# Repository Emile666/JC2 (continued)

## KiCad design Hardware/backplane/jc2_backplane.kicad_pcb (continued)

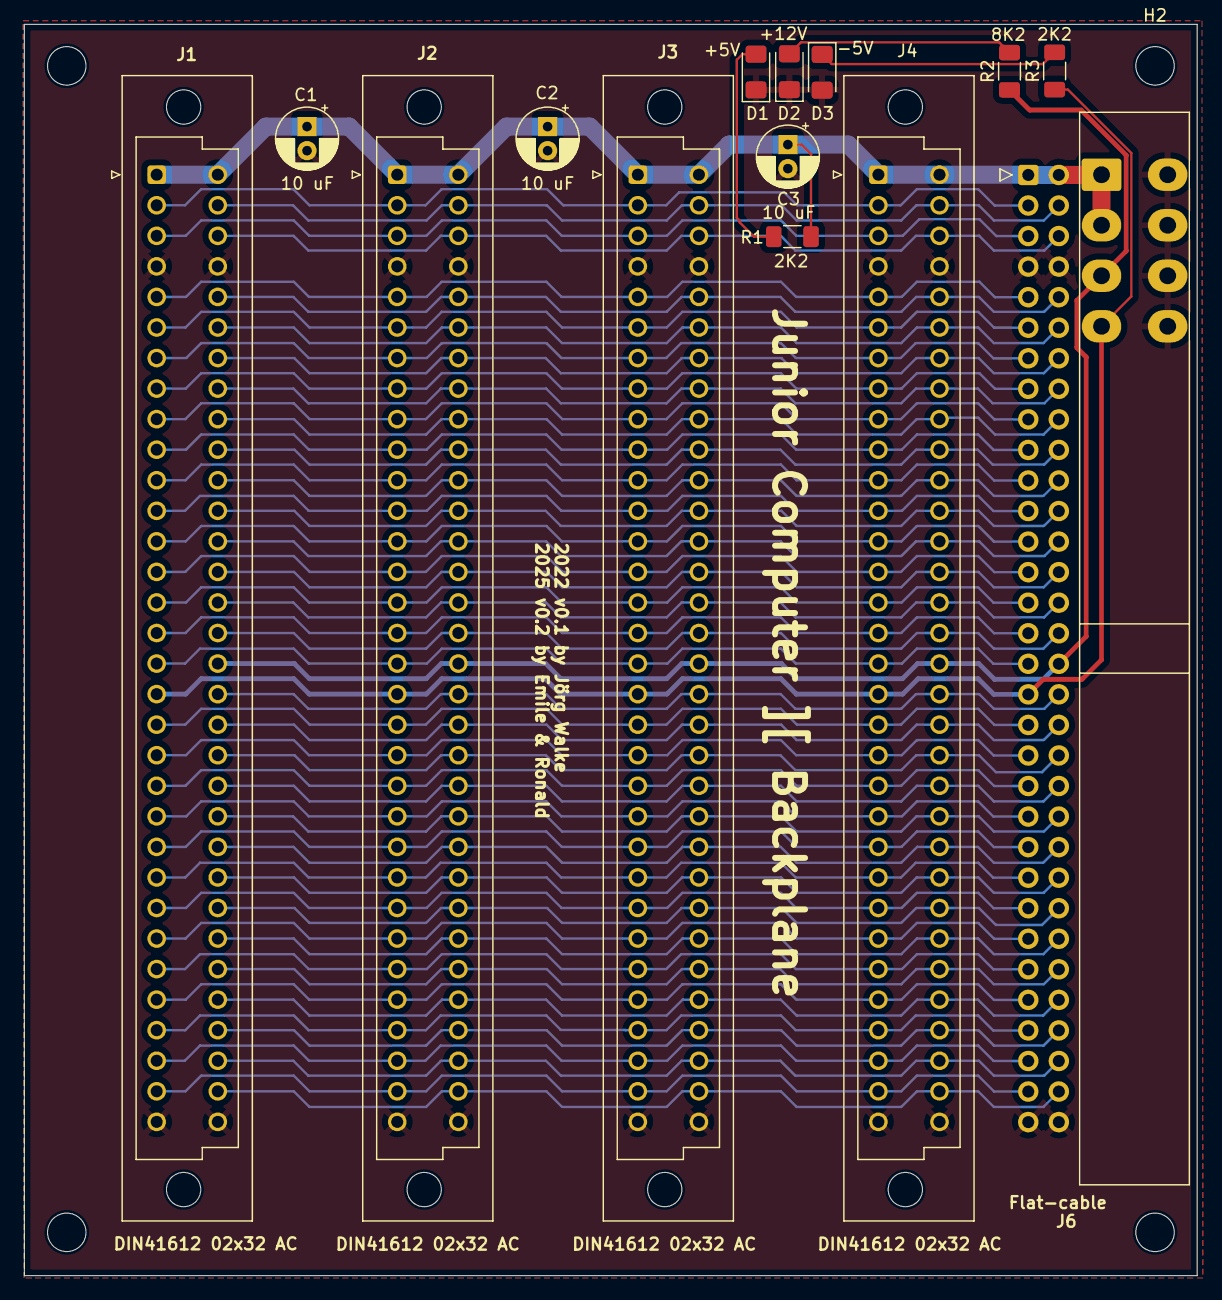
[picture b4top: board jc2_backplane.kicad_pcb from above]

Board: 2 copper layers, 97.5 x 104.0 mm, 19 parts (1 on the bottom side), 63 nets.

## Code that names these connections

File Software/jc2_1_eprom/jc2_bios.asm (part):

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		LDA     #$21
		TAY
		STA     PBDD		; turn speaker on
BEEPLOOP	STY     PBD		; set PB0 high
		LDA     #$01
		JSR     DELAY		; delay of ~1ms
		DEY
		STY	PBD		; set PB0 low
		LDA	#$01
		JSR	DELAY		; delay of ~1ms
		LDY	#$21
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; Jump to original Junior Computer reset vector ********************************

;*******************************************************************************
JCRESET		LDA	#$06			; set PB5 = L (WRITE)
		STA	PBD
		SEI
		JSR     INITVECT
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                BNE     INIT_VIA        ; is standard input device still TTY?
                JSR	DETECT_ASCIIKBD	; yes, check if ASCII keyboard available, else skip it
INIT_VIA	LDY	#PORTB
		LDA	#%01001110	; SDA=0,/CAS_MOT=1,CAS_SENSE=0,CAS_WR=0,/SPI_LOAD=1,SPI_CS=1,/SND_WE=1,SCL=0
		STA	VIA_STATUS	; store current PortB output status
		STA	(IOBASE),Y	; set SDA as input to pull it high, set SCL as input to pull it high
		LDY	#DDRB		; initialize data direction of port B
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		BEQ	READMODE	; yes, check if data available
		JSR	SETPPORTIN	; no, first set parallel port as an input
READMODE	CLC			; set to no char present
		BIT	WRDC		; test PA7 (DATA_AVAIL)
		BVC	NODATA		; no new data, just exit with C = 0
		LDA	WRDC		; clear PA7 flag
		LDA	PAD		; load keyboard ASCII code from port A
		AND	#%01111111	; clear MSB
DATA_AVAIL	SEC			; and set C = 1, char present
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		LDA	#$BE		; initialize handshake line I/O on port b
		CMP	PBDD		; already initialized?
		BEQ	SETHSK		; yes, just set output values
		STA	PBDD		; no, PB7 = /strobe, PB6 = busy, PB5 = r/w, PB0 = speaker off
SETHSK		LDA	#$86		; set handshake lines to their initial values
		STA	PBD		; r/w = L, strobe = H, PB1,PB2 = H -> hex-kbd disabled; speaker = H
		LDA	#$FF		; all port A lines are outputs
		STA	PADD
		PLA			; reload character in A
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
PPORTIN		JSR	SETPPORTIN	; set parallel port as input
		CLC
		BIT	PBD		; check if /STROBE = 0
		BMI	NOSTROBE	; no, just exit with C = 0
STROBE?		BIT	PBD		; yes, wait for strobe to come high again
		BMI	STROBE?
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		STA	PADD
		LDA	#$3E		; initialize port B bits for read operation
		STA	PBDD
		LDA	#$26		; set PB5 = H (READ)
		STA	PBD
		STA	WRDC		; set PA7 raising edge detection, no interrupt
		LDA	WRDC		; clear interrupt flag
		RTS

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		AND	(IOBASE),Y		; shift register full?
		BEQ	SPI_WRITE1		; no, check again
		LDY	#PORTB
		LDA	#$42 			; SPI_CS = L; LOAD_DATA = 0
		STA	(IOBASE),Y		; load data into shift register
		LDA	#$4A 			; SPI_CS = L; LOAD_DATA = 1
		STA	(IOBASE),Y		; data is now in shift register
		BNE	SPI_RESET               ; branch always

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
SD_WAIT_RESP3	LDY	#$00
READ_RESP3	JSR	SD_WAIT_RESP		; yes, receive 4 response bytes
		STA	SD_PB3,Y		; store response bytes in PB0..3
		INY
		CPY	#$04
		BNE	READ_RESP3
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		LDY	#PORTA			; and write it to the card
		STA	(IOBASE),Y		; output data to shift register
		DEY				; set for PORTB
		LDA	#$42 			; SPI_CS = L; LOAD_DATA = 0
		STA	(IOBASE),Y		; load data into shift register
		LDA	#$4A 			; SPI_CS = L; LOAD_DATA = 1
		STA	(IOBASE),Y		; data is now in shift register
		LDY 	#SR
		LDA	(IOBASE),Y		; and start clk'ing
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		LDY #>TXT_MSEC
		JSR SPRINT	    	; print
PRENDOK		SEC			; C=1, no error
		RTS			; return if BSY=0 and RDY=DSC=1
	
CFWLPTO		LDX #<TXT_HWERR     	; Print HW error
		LDY #>TXT_HWERR
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
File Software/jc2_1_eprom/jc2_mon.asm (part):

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        JMP     START

; RESET vector 6502
RESET   LDA     #$3F        ; PB5---PB0
        STA     PBDD        ; IS output
        LDA     #$04        ; Reset P-Register
        STA     PREG
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;       a function of BYTES.
;       The next subroutine AK scans the keyboard, it returns with A=0 if no
;       key was pressed and with A > 0 if a key was pressed.
;       When SCAND or SCANDS are exit, PA0..PA7 are set to input.
;----------------------------------------------------------------------------
SCAND   LDY     #$00
        LDA     (POINT),Y   ; Get data specified by point
        STA     INH

SCANDS  LDA     #$7F
        STA     PADD        ; PA0..PA6 is output
        LDX     #$08        ; Enable display
        LDY     BYTES       ; Fetch length from bytes

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        JSR     SHOW        ; If yes, output 3rd byte

SCDSB   LDA     #$00
        STA     PADD        ; PA0..PA7 is input
AK      LDY     #$03        ; Scan 3 rows
        LDX     #$00        ; Reset row counter

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
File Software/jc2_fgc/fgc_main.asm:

; ------------------------------------------------------------------------------
; Floppy/Graphics-Controller BIOS V0.2.2 for the Junior Computer ][, by Emile
; V0.2.0 by Joerg Walke.
;
; EPROM code is divided into 16 pages of 1K, called BANK 00..31. The lower 16K
; of the FGC - BANK 00..BANK 15 - are mirrored to the higher 16K - BANK 16..BANK 31.
; JP4 now selects which 16 KB ROM area will be used:
; 1-2 (27C256) = lower 16 KB ROM area, 2-3 (28C256) = higher 16 KB ROM area
;
; FGC_VPU      : BANK 00   $0000-$03FF
;                BANK 16   $4000-$43FF (Mirror)
;
; FGC_VPU_CMD  : BANK 01   $0400-$07FF
;                BANK 17   $4400-$47FF (Mirror)
;                
; FGC_FLOPPY     BANK 02 - 03	$0800-$0FFF (not yet implemented)
; FGC_FLOPPY     BANK 18 - 19	$4800-$4CFF (Mirror)
;
; FGC_CHAR_ROM : BANK 04 - 07	$1000-$1FFF
;                BANK 20 - 23	$5000-$5FFF  (Mirror)
;               
; EMPTY          BANK 08..14
; EMPTY          BANK 24..30
;
; FGC_INIT_ROM : BANK 15   $3C00-$3FFF
;                BANK 31   $7C00-$7FFF  (Mirror)
; ------------------------------------------------------------------------------
VERMAIN   	EQU     '0'    			; FGC main version
VERPSUB    	EQU     '2'    			; FGC primary sub version
VERSSUB		EQU	'2'			; FGC secondary sub version

; List Of Changes **************************************************************
; V0.2  : Original version from Joerg Walke, May 14th, 2025
; V0.2.1: Adapted for MADS by Emile, eprom binary is now identical to Joerg's version ($0000-$3FFF)
; V0.2.2: source include files reorganised, one system wide definition of ZP vars
; ******************************************************************************
		OPT h- ; do not add file header
		OPT f+ ; save as single block

		ICL "jc2_macros.inc"		; JC2 macro definitions for MADS
		ICL "jc2_defines.inc"		; JC2 system-defines
		ICL "jc2_constants.inc"		; JC2 constants
		ICL "jc2_bios_calls.inc"	; JC2 BIOS routines
		
PROG_START	EQU	$0200	      		; Program Start Address in RAM
PS2NO_KBD       EQU     $06           		; No keyboard selected

; ------------------------------------------------------------------------------
; EPROM Code Size is from $0000 - $3FFF (lowest 16 KB) and from
; $4000 - $7FFF for the highest 16 KB. Every 1 KB page is assembed to 
; base-address FGC_BASE ($1000). The active page is selected by the 
; 8255 PIA PORTC PC7,PC2,PC1,PC0 ($100E).
; ------------------------------------------------------------------------------
		ORG	$0000			; Page 0, Eprom Start address
		ICL 	"b00_vpu.asm"		; VPU Driver

		ORG	$0400			; Page 1
		ICL 	"b01_vpu_cmd.asm"	; VPU Command Driver

		; Pages 2 & 3: Floppy Disc Controller (FDC)
		ORG	$0800			; Pages 2 & 3
		ICL 	"b02_fdc_init.asm"	; FDC, not implemented yet

		ORG	$1000			; Page 4
		ICL 	"b04_char_tbl.asm"	; VPU Character table
		
		ORG	$3C00			; Page 15
		ICL 	"b15_vpu_init.asm"	; VPU Init
		
		ORG	$7FFF
		.byte	$FF			; Make .bin file 32K
		END

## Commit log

2025-03-04 First version for Github
2025-03-04 README.md update
2025-03-04 jc2_mon added
2025-03-04 jc2_mmu .pld file added
2025-03-06 atf1504 programming doc added
2025-03-20 Updates of mmu and backplane HW
2025-03-20 IDE-CF Firmware update (V0.21)
2025-03-24 cf_ide update
2025-04-16 JC2 1 Eprom dir added
    Monitor, Basic and BIOS .asm files are now integrated into one 32K eprom. It is still BIOS v1.1.4 with Basic V2.25.
    This eprom version will only work with the ATF1504 V0.40 firmware and with the A13 and A14 eprom HW patch.
2025-04-16 All constants & defines to jc2_defines.inc
    jc2_defines.inc now contains all constants and address defines for the Basic, Bios and Monitor. It clearly shows multiple use of zero-page addresses and this needs to be sorted out.
    The resulting 32K .bin file compared the same to a merged Basic / Bios v1.1.4 / Monitor version.
2025-04-21 V1.2.0: Software now supports CF-IDE Interface
    Many changes were made to the existing software, such as a new mkboot, a new boot.sys, a new BIOS and an integrated EPROM, combining BASIC, BIOS and Monitor.
2025-04-24 Rambank atf1504 firmware V0.32 bugfix
    The memory behind the Monitor ROM was only 256 bytes instead of 1 KB. This is corrected in V0.32.
2025-04-27 JC2 V1.2.0 1-eprom version finalized
    On an existing JC2 (v3.1b) board, A13 and A14 need to be added to the eprom and ATF1504 MMU firmware should be updated to V0.40.
2025-05-08 V1.2.1 BIOS 1 Eprom + Firmware V0.40
    Integrates Basic, Monitor + BIOS into 1 27C256 Eprom on JC2 board v3.1.b. The Basic Eprom on the Language-IO card should be removed. The V0.40 firmware is meant for the ATF1504 MMU and is now able to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
    Other notable changes are:
    - Basic update: patches from V2.22 were added + I2Cout, I2Cin() and DOS commands were added. Also the (destructive) RAM-test is disabled, so that it now works together with other programs
    - MKboot and boot.sys updated: now boots from CF-card, boot.sys contains lots of debug messages, to be removed in a future version
    - Switching from DOS (boot.sys) to Basic and back is added
2025-05-14 JC2 Main-board V4.1 files added
2025-05-19 BIOS V1.2.2 with Basic V2.27
    Trying to integrate BIOS, boot.sys and Basic. There's too much overlap on zero-page and buffers between these programs. It was never meant to work together, this version is a try-out to integrate all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
2025-05-24 V1.23: Basic LOAD bugfixes
    1) Basic used ADRL/ADRL and ADREL/ADREH, but in BIOS they had other names. I moved these vars to other locations, breaking the relation between them. So I added them back with the proper BIOS names.
    2) NUML/NUMH and MODE were not init. in BASIC LOAD. In previous versions, the boot.sys routine gave these memory locations a value and this happened to work. With a proper allocations of variables, t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
2025-06-07 Boot.sys V0.23 added
    This is work in progress!
    - The current file (3350+ lines) is split into separate smaller files
    - Various macro's added to macros.inc, I hope to make to code more readable this way.
    - All variables are now defined in defines.inc
    - Added boot_v023.lst and boot_023.sys for reference purposes.
    - A ROM2RAM file has been added as well, this only works with 1-eprom BIOS V1.23! It copies ROM 2 RAM and adds debug routines to the CF-IDE driver routines CF_RD_LBLK and CF_RD_LBLK_BUF. Same for CF_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
2025-06-10 boot.sys V0.24 + mkbootcf V0.2 bug-fixes
    - Mkbootcf now has a NUM32 bugfix (NUM32 overlapped with other vars)
    - boot.sys now has a working .BAS load function
    - Bug-fix mkdir run after dir command
    - Total KB free added to DIR command
2025-06-16 IO2 board added
    The original IO board is upgraded with this IO2 board: KiCad files, .pdf schematic, Gerber files and .pld files.
2025-06-17 boot.sys V0.2.5: DEL command added
2025-07-18 6502 Protocol Decoder added
    The 6502 protocol decoder may be used with the Sigrok project. However I used it with Gusmanb's Logic-Analyzer software.
2025-07-18 More screenshots added
    All addressing modes have now at least one screenshot verifying the operation of the decoder.
2025-07-18 Bugfix opcode Fetch read timing
    Opcode Fetch should also be done after PHI2 falling edge. When read after rising edge, in some (rare) cases it led to a wrong disassembly.
2025-07-26 V1.2.4: Sound added + PORT support for IO2 board
2025-07-29 boot.sys V0.26
    This version support LOAD and SAVE from BASIC.
2025-08-02 V0.2.7: Couple of bug-fixes
    Path-name string was incorrect with CD command use in subdir and with an unknown command.
2025-08-03 V0.28: RAM-bank enabled for BASIC
    1) Enabling RAM-BANK 4 for BASIC and RAM-BANK 0 for DOS. Now Basic programs can load all the way up to $AFFF.
    2) Another bug-fix on DOS path-name.
    3) PC-application Basic_converter.exe added
2025-08-04 V0.29: DOS now in separate RAM-BANK
    BASIC related DOS functions are now copied into the Monitor RAM area.
    When BASIC is enabled, the DOS itself is hidden from Basic: RAM-BANK 4 is selected for BASIC and DOS is located in RAM-BANK 0.
    Switching to DOS enables RAM-BANK 0 again.
2025-08-04 rom2ram updated
    ROM2RAM is a program that, when loaded via XModem, enables debugging info for the CF device driver routines. It shows LBA and buffers for every Read and Write actions from and to the CF-card. It also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
    It does so by copying BIOS to RAM and then patch it.
2025-08-06 FGC ROM: v0.21 added
    These files build the latest FGC eprom version from Joerg Walke, 14-05-2025. A binary file-compare showed no differences for the first 16 KB of the .bin file, highest 16 KB are not build yet.
    Note that this version does NOT run yet on the JC2 v4.1 system, it only served as a reference and baseline for future revisions.
2025-08-14 V0.30 boot.sys
    - Improved CF-card error-checking & handling
    - Volume-label printing added for root-dir
    - CF device-driver routines now in Monitor RAM
2025-08-22 V0.31 boot.sys: FAT bug-fixes
    - Bug-fix mkdir buffer not cleared.
    - Bug-fixes update_fat_table, link_fat_entry and read_fat_entry
2025-08-27 BIOS V1.25 + FGC V0.22 + Boot.sys V0.32
    Reorganisation of .inc files. There's now a top-level directory with all .inc files together. All programs now have one and the same address defines.
    First version of FGC V0.22, does not work yet!
    boot.sys V0.32 no functional changes.
    BIOS V1.25 now contains bug-fixes for CF-routines (CFWAIT).
2025-10-30 Logic Analyzer mos6502 update
